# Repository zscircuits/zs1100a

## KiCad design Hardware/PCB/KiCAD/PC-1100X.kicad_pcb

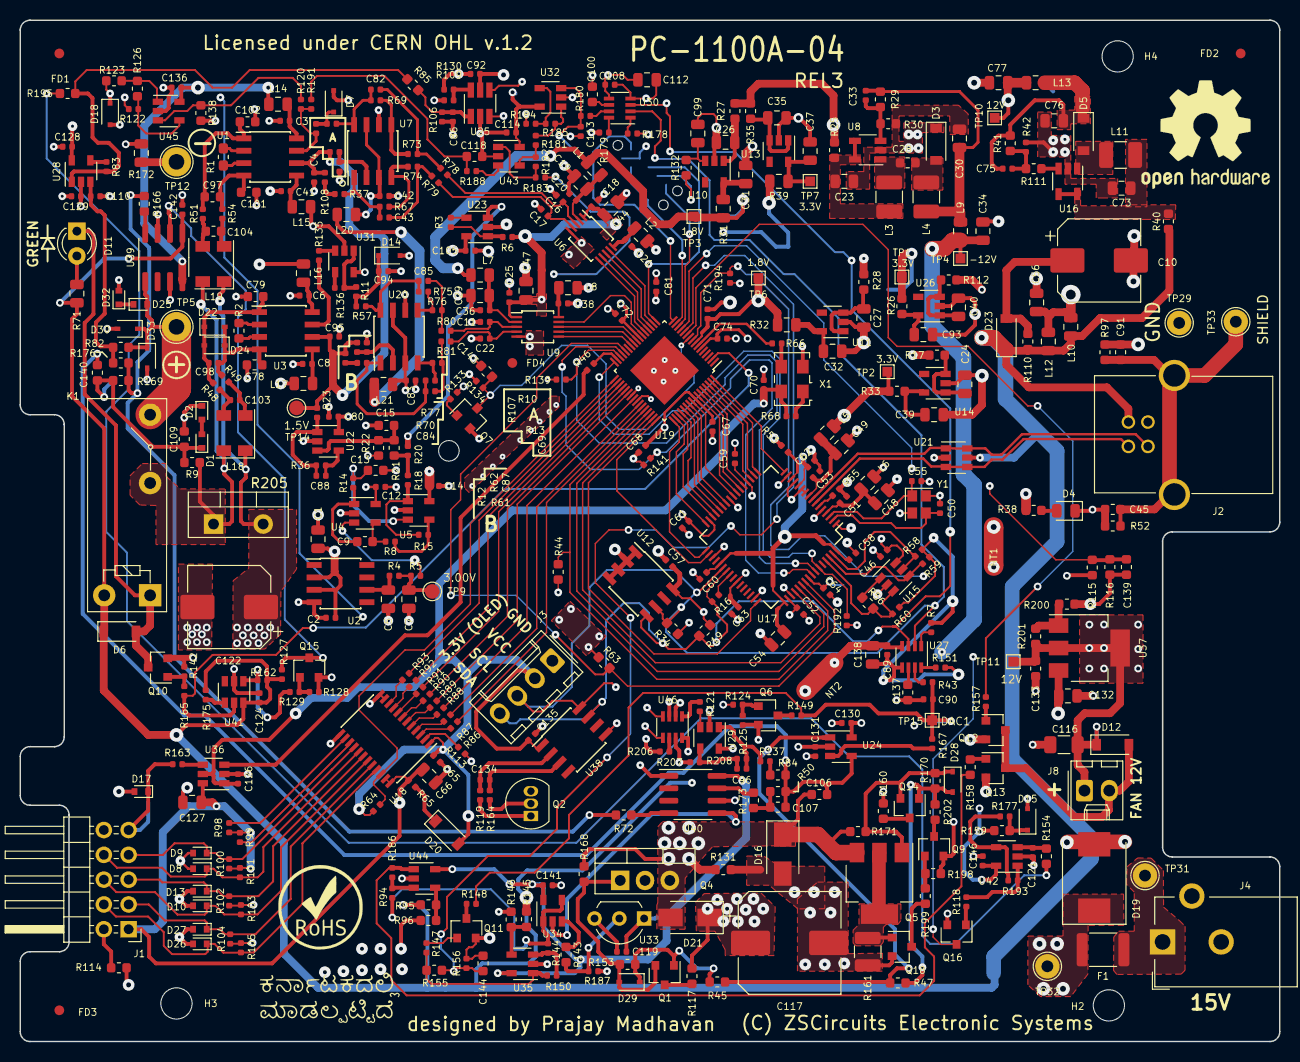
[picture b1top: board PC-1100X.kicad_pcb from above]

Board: 4 copper layers, 129.0 x 104.6 mm, 528 parts (0 on the bottom side), 290 nets.

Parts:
C1, C5, C7, C19, C24, C26, C27, C29, C30, C31, C32, C35, C37, C39, C40, C44, C47, C48, C49, C54, C66, C76, C93, C99, C112, C127, C132, C138: 10uF; C_0805_2012Metric
C2, C3, C6, C8, C12, C14, C21, C36, C38, C41, C42, C46, C52, C57, C58, C59, C60, C61, C62, C63, C64, C65, C67, C68, C70, C71, C72, C74, C80, C81, C83, C86, C89, C90, C92, C105, C108, C113, C114, C119, C121, C124, C126, C130, C131, C135, C136, C141, C142, C146: 0.1uF; C_0402_1005Metric
C4, C18, C25, C84, C85, C95, C96, C98, C103: 1000pF; C_0402_1005Metric
C9, C13, C15, C28, C45, C91, C100, C109, C118, C133, C137: 1uF; C_0603_1608Metric
C10, C122: 220uF; CP_Elec_8x10
C11, C16, C17, C22: 2200pF; C_0402_1005Metric
C20, C51, C53, C88, C94, C134: 100pF; C_0402_1005Metric
C23, C34, C56, C73, C77: 22uF; C_0805_2012Metric
C33, C43, C75, C82: 220pF; C_0402_1005Metric
C50, C55: 12pF; C_0402_1005Metric
C69, C87, C110, C128, C129: 10000pF; C_0402_1005Metric
C78, C79, C97, C101, C102, C104, C107: 100pF; C_0603_1608Metric
C106, C139, C140, C143, C144: 4700pF; C_0603_1608Metric
C116: 47uF; C_1206_3216Metric
C117: 470uF; CP_Elec_10x10
D1, D2, D8, D9, D10, D13, D17, D25, D26, D27, D32: ESD5Z12T1G; D_SOD-523
D3, D5: MBR0520; D_SOD-123
D4: LED; LED_0805_2012Metric
D6, D12, D20, D23: CDBW140-G; D_SOD-123
D7: MM3Z5V6T1G; D_SOD-323F
D11: LED GREEN; LED_D3.0mm
D14: MM3Z4V3T1G; D_SOD-323F
D15: MM3Z7V5ST1G; D_SOD-323F
D16, D21: SK56A-LTP; D_SMA
D18: MM3Z4V7ST1G; D_SOD-323F
D19: SMDJ20A; D_SMC
D22, D24, D28, D29: D_Schottky; D_SOD-323
D30, D33: 1N4148WSF-7; D_SOD-323
F1: Polyfuse; R_1812_4532Metric
FD1, FD2, FD3, FD4: FIDUCIAL; Fiducial_1mm_Dia_2.54mm_Outer_CopperTop_Paste
H2, H3, H4: MountingHole; MountingHole_3.2mm_M3
H5: MountingHole; MountingHole_2.1mm
HS1, HS2: Heatsink; NONE
J1: Conn_02x05_Odd_Even; PinHeader_2x05_P2.54mm_Horizontal
J2: USB_B; USB2p0_TypeB_Standard
J3: Conn_01x04_Male; Molex_KK-254_AE-6410-04A_1x04_P2.54mm_Vertical
J4: Barrel_Jack_Switch; BarrelJack_CUI_PJ-102AH_Horizontal_3D
J5: Conn_02x05_Counter_Clockwise; Tag-Connect_TC2050-IDC-NL_2x05_P1.27mm_Vertical
J8: Fan; Molex_KK-254_AE-6410-02A_1x02_P2.54mm_Vertical
K1: G5NB; Relay_SPST_Omron-G5NB
L1, L2, L5, L6, L7, L8, L9, L10, L12, L13, L14, L15, L16, L17, L20, L21: FB; L_0805_2012Metric
L3, L4, L11: 10uH; L_1210_3225Metric_Pad1.42x2.65mm_HandSolder
L18, L19: choke; CommonModeChoke-4Pin_4.5x3.2mm
LG2: RoHS; Rohs_09mm
LG4: Made in KA; MadeInKA_15mmx6mm
LOGO1: Logo_Open_Hardware_Small; OSHW-Logo2_14.6x12mm_SilkScreen
NT1, NT2: Net-Tie_2; NetTie-2_SMD_Pad2.0mm
P1, P3, P4, P5, P6, P7, P8, P9, P10, P11, P12, P13, P14, P15, P16, P17, P18, P19: DUMMY; NONE
P2: Aluminium Case; NONE
Q1, Q6, Q7, Q11, Q12, Q13, Q16, Q18: BC817; SOT-23
Q2: 2N3906; TO-92_Inline
Q4: TIP33C; TO-220-3_Vertical
Q5: FZT1151ATA; SOT-223-3_TabPin2
Q9, Q14: BC807; SOT-23
Q10, Q15: BSS138; SOT-23
R1: 20k00; R_0603_1608Metric_Pad1.05x0.95mm_HandSolder
R2: 56R2; R_0603_1608Metric
R3, R14, R36, R48, R49, R51, R53, R54, R83, R94, R109, R113, R119, R121, R130, R135, R136, R144, R164, R181, R188: 1k; R_0402_1005Metric
R4, R73, R74, R76, R77, R78, R79, R80, R81: 22R; R_0402_1005Metric
R5, R13, R15, R20, R62, R137, R148, R149: 0R; R_0402_1005Metric
R6, R18, R23: 2R; R_0402_1005Metric
R7, R43, R151, R157, R167, R178, R179, R180, R194: 3.3k; R_0402_1005Metric
R8, R185: 20k; R_0402_1005Metric
R9, R17, R25, R26, R27, R28, R33, R35, R40, R112, R166, R173: 0R; R_0603_1608Metric
R10, R37, R107, R108: 499R; R_0402_1005Metric
R11, R12: 1k60; R_0402_1005Metric
R16, R46, R65, R66, R86, R87, R88, R89, R90, R91, R92, R93, R163: 33R; R_0402_1005Metric
R19, R34, R45, R47: 2k2; R_0603_1608Metric
R21, R22, R198, R199: 3k3; R_0603_1608Metric
R29: 82k; R_0603_1608Metric
R30, R44, R52, R63, R72, R95, R97, R111, R126, R132, R138, R145, R155: 10k; R_0603_1608Metric
R31, R32, R39, R172: 0R; R_0805_2012Metric
R38: 330R; R_0603_1608Metric
R41: 105k; R_0603_1608Metric
R42, R55: 12k; R_0402_1005Metric
R50: 15k00; R_0603_1608Metric
R56, R116, R146, R200, R202: 2k; R_0603_1608Metric
R57, R61: 1k20; R_0402_1005Metric
R58, R59, R60, R64, R68, R120, R122, R139, R141, R162, R177, R184, R191, R192, R206, R207: 10k; R_0402_1005Metric
R67, R69: 1k00; R_0402_1005Metric
R70, R75: 6k80; R_0402_1005Metric
R71: 680R; R_0805_2012Metric
R82, R96, R123, R131, R143, R154, R159, R169, R176, R195: 1k; R_0603_1608Metric
R84, R85: 10k00; R_0603_1608Metric
R98, R99, R100, R101, R102, R103, R104, R105, R128, R142, R182, R193: 100k; R_0402_1005Metric
R106: 2k10; R_0402_1005Metric
R110, R114, R117, R160: 10R; R_0603_1608Metric
R115, R158: 6k8; R_0603_1608Metric
R118, R124, R125, R133, R147, R208: 33k; R_0402_1005Metric
R127, R129, R156, R165: 4k3; R_0402_1005Metric
R134: 3k3; R_0402_1005Metric
R150, R175, R186, R187: 47k; R_0402_1005Metric
R153, R170: 5k6; R_0603_1608Metric
R161: 1R; R_1210_3225Metric
R168, R171: 150R; R_0603_1608Metric
R183: 100R; R_0402_1005Metric
R201: 220R; R_0603_1608Metric
R205: 1R00; TO-220-2_Vertical
TP1, TP2, TP3, TP4, TP6, TP7, TP10: TestPoint; TestPoint_Pad_1.0x1.0mm
TP5, TP12: TestPoint; TestPoint_Loop_D2.60mm_Drill1.6mm_Beaded
TP8, TP9, TP13, TP14, TP16, TP17, TP18, TP19, TP20, TP21, TP22, TP23, TP24, TP25, TP26, TP27, TP28: TestPoint; TestPoint_Pad_D1.5mm
TP11, TP15: TP; TestPoint_Pad_1.0x1.0mm
TP29, TP31, TP32, TP33: TestPoint; TestPoint_THTPad_D2.5mm_Drill1.2mm
U1, U3, U40: AD8422ARZ; SOIC-8_3.9x4.9mm_P1.27mm
U2: LT1461CCS8-3; SOIC-8_3.9x4.9mm_P1.27mm
U4: OPA333xxDBV; SOT-23-5
U5, U22, U23: THS4281DBVT; SOT-23-5
U6, U9: MCP33131D-10-I/MS; TSSOP-10_3x3mm_P0.5mm
U7, U20: THS4521; SOIC-8_3.9x4.9mm_P1.27mm
U8: LT1931; TSOT-23-5
U10, U11: TLV70218_SOT23-5; SOT-23-5
U12: ATSHA204A-SSHDA-T; SOIC-8_3.9x4.9mm_P1.27mm
U13, U14, U26: TLV70233_SOT23-5; SOT-23-5
U15: 93LC46B; SOT-23-6
U16: LT1613; TSOT-23-5
U17: FT2232H; LQFP-64_10x10mm_P0.5mm
U18: SN74LVC8T245; TSSOP-24_4.4x7.8mm_P0.65mm
U19: 5M160ZE64I5N; EQFP-64_1EP_7x7mm_P0.4mm_SM
U21: USBLC6-2SC6Y; SOT-23-6
U24, U28, U29, U31, U45: OPA196; SOT-23-5
U25: MCP3425A0T-ECH; SOT-23-6_Handsoldering
U27, U30: LTC2631ITS8-LM12; SOT-23-8
U32, U34, U35, U42, U43, U44: TLV9301IDBVR; SOT-23-5
U33: LM35DZ/NOPB; TO-92L_Inline_Wide
U36: SN74LVC1T45DBVR; SOT-23-6
U37: LM317_3PinPackage; SOT-223-3_TabPin2
U38: TMP411; SOIC-8_3.9x4.9mm_P1.27mm
U39: ADG417BR; SOIC-8_3.9x4.9mm_P1.27mm
U41: TPS3808; SOT-23-6
U46: CAT5171; SOT-23-8
X1: 64MHz; Oscillator_SMD_TXC_7C-4Pin_5.0x3.2mm
Y1: Crystal 12MHz; Crystal_SMD_2520-4Pin_2.5x2.0mm

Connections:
+1V8: C71.1, C81.1, R32.1, TP6.1, TP20.1, U19.8, U19.41
+3V3: C92.1, C108.1, C112.1, L20.1, L21.1, R26.2, R179.1, TP1.1, TP25.1, U25.5, U30.5
+5V: C1.2, C2.2, C12.1, C14.1, C56.1, C80.1, C105.1, L10.2, L12.2, R38.1, U2.2, U2.3, U4.5, U5.5, U22.5, U23.5
+12P: C116.1, C133.1, D12.1, J8.1, R201.1, TP11.1, TP28.1, U37.2
+12V: C77.1, C114.1, C119.1, C128.1, C130.1, C136.1, C141.1, C146.1, L13.2, L14.1, L16.1, R159.1, TP10.1, TP24.1, U24.5, U28.5, U29.5, U31.5, U32.5, U33.1, U34.5, U35.5, U39.4, U40.8, U42.5, U43.5, U44.5, U45.5
+15V: C117.1, C132.1, D19.1, D21.1, F1.1, Q4.2, Q9.2, R115.1, R117.1, R198.2, TP32.1, U37.3
-12V: C34.1, C129.2, C131.1, L9.2, L15.2, L17.2, TP4.1, TP22.1, U24.2, U28.2, U29.2, U31.2, U34.2, U40.5
/ADC_System/ADC1_CONVST: U6.6, U19.21
/ADC_System/ADC1_DIN: U6.9, U19.18
/ADC_System/ADC1_DOUT: U6.7, U19.20
/ADC_System/ADC1_SCLK: U6.8, U19.19
/ADC_System/ADC2_CONVST: U9.6, U19.26
/ADC_System/ADC2_DIN: U9.9, U19.22
/ADC_System/ADC2_DOUT: U9.7, U19.25
/ADC_System/ADC2_SCLK: U9.8, U19.24
/ADC_System/ADC_REF_3V: C18.1, C25.1, C44.1, C47.1, R6.2, TP13.1, U6.1, U9.1
/ADC_System/CURR_LIM_SETV: R181.1, R185.2, U32.1
/ADC_System/DIV_OUT: R121.2, U46.1
/ADC_System/I2C_SCL_3V3: J3.3, R34.2, U12.6, U17.38, U25.3, U27.2, U30.2, U38.8, U46.4
/ADC_System/I2C_SDA_3V3: J3.4, R16.2, R19.2, U12.5, U17.39, U25.4, U27.3, U30.3, U38.7, U46.5
/ADC_System/ILIM_P: C118.1, R188.1, R191.2
/ADC_System/LTC_REF_CAP: C5.2, R4.1, U2.6
/ADC_System/SAR1_BUF_REF: C4.1, C95.1, R12.1, R13.1, R23.1, R62.1, R108.1, R122.1, TP14.1, TP18.1, U1.6, U3.6
/ADC_System/SAR1_INM: C17.1, R79.2, U6.4
/ADC_System/SAR1_INP: C16.1, R78.2, U6.3
/ADC_System/SENSE_M: K1.2, L18.4, L19.4, R9.2, R205.1
/ADC_System/SENSE_P: C106.1, C122.1, D16.1, D21.2, L18.1, L19.1, Q4.3, Q5.3, R131.1, R168.1, R171.2, R205.2
/CPLD_USB/ACBUS0: U17.26, U19.55
/CPLD_USB/ACBUS1: U17.27, U19.54
/CPLD_USB/ACBUS2: U17.28, U19.53
/CPLD_USB/ACBUS3: U17.29, U19.52
/CPLD_USB/ACBUS4: U17.30, U19.51
/CPLD_USB/ACBUS5: U17.32, U19.50
/CPLD_USB/ACBUS6: U17.33, U19.49
/CPLD_USB/ACBUS7: U17.34, U19.48
/CPLD_USB/ADBUS0: U17.16, U19.64
/CPLD_USB/ADBUS1: U17.17, U19.63
/CPLD_USB/ADBUS2: U17.18, U19.62
/CPLD_USB/ADBUS3: U17.19, U19.61
/CPLD_USB/ADBUS4: U17.21, U19.60
/CPLD_USB/ADBUS5: U17.22, U19.59
/CPLD_USB/ADBUS6: U17.23, U19.58
/CPLD_USB/ADBUS7: U17.24, U19.56
/CPLD_USB/BCBUS0: U17.48, U19.47
/CPLD_USB/BCBUS1: U17.52, U19.46
/CPLD_USB/BCBUS2: U17.53, U19.45
/CPLD_USB/BCBUS3: R44.2, U17.54, U19.44
/CPLD_USB/BCBUS4: R63.2, U17.55, U19.28
/CPLD_USB/BCBUS5: R141.2, U17.57, U19.29
/CPLD_USB/BCBUS6: R139.2, U17.58, U19.30
/CPLD_USB/BCBUS7: R192.2, U17.59, U19.32
/CPLD_USB/CLK_OUT: D17.1, J1.9, R163.1, TP16.1
/CPLD_USB/DIG0: R86.2, U19.43
/CPLD_USB/DIG0_IN: D26.1, J1.4, R105.2, U18.21
/CPLD_USB/DIG1: R87.2, U19.42
/CPLD_USB/DIG1_IN: D27.1, J1.3, R104.2, U18.20
/CPLD_USB/DIG2: R88.2, U19.40
/CPLD_USB/DIG2_IN: D10.1, J1.6, R103.2, U18.19
/CPLD_USB/DIG3: R89.2, U19.38
/CPLD_USB/DIG3_IN: D13.1, J1.5, R102.2, U18.18
/CPLD_USB/DIG4: R90.2, U19.37
/CPLD_USB/DIG4_IN: D8.1, J1.8, R101.2, U18.17
/CPLD_USB/DIG5: R91.2, U19.36
/CPLD_USB/DIG5_IN: D9.1, J1.7, R100.2, U18.16
/CPLD_USB/DIG6: R92.2, U19.35
/CPLD_USB/DIG7: R93.2, U19.34
/CPLD_USB/EE_CLK: R59.1, U15.4, U17.62
/CPLD_USB/EE_CS: R58.1, U15.5, U17.63
/CPLD_USB/EE_DATA: R56.1, R60.1, U15.3, U17.61
/CPLD_USB/IO_02: R165.1, U19.2, U41.5
/CPLD_USB/IO_09: Q16.3, R194.2, U19.9
/CPLD_USB/IO_10: C143.2, Q7.3, R134.2, U19.10
/CPLD_USB/IO_12: C144.2, R155.2, R156.1, U19.12
/CPLD_USB/IO_13: C139.2, R115.2, R116.1, U19.13
/CPLD_USB/LOGIC_VCC: C66.1, C127.1, J1.1, R65.2, R98.1, R99.1, R100.1, R101.1, U18.23, U18.24, U36.6
/CPLD_USB/TCK: J5.1, U19.16
/CPLD_USB/TDI: J5.9, U19.15
/CPLD_USB/TDO: J5.3, U19.17
/CPLD_USB/TMS: J5.5, U19.14
/CPLD_USB/USB_D+: J2.3, U17.8, U21.1, U21.6
/CPLD_USB/USB_D-: J2.2, U17.7, U21.3, U21.4
/CPLD_USB/VPHY: C48.1, C51.1, L6.2, U17.4
/CPLD_USB/VPLL: C49.1, C53.1, L5.2, U17.9
/CPLD_USB/~DIG_OE: R64.2, U18.22, U19.33
/OutputDriver/CLAMP_IN: R124.1, R133.1, R183.1
/OutputDriver/C_FB: C106.2, C107.2, C140.2, R50.1, R84.1, U24.4
/OutputDriver/FAN_CTRL: R94.1, R144.1, TP17.1, U34.1, U34.4
/OutputDriver/FAN_EN_3V3: R157.1, U19.11
/OutputDriver/GND_SENSE: C86.2, R106.2, R109.1, R172.2, U40.1
/OutputDriver/MUX_CONTROL: Q15.3, R127.2, U39.6
/OutputDriver/OUTPUT: D25.2, D30.1, D33.1, K1.3, R82.1, TP5.1, U39.1
/OutputDriver/VBUFF_SENSE: R154.2, R195.2
/OutputDriver/V_FB: R72.2, R166.1, R169.2, R176.1
GND: C1.1, C2.1, C3.2, C4.2, C5.1, C6.2, C7.1, C8.2, C10.2, C11.2, C12.2, C13.2, C14.2, C15.2, C16.2, C17.2, C18.2, C19.2, C20.2, C21.2, C22.2, C23.2, C24.2, C25.2, C26.2, C27.2, C29.2, C30.2, C31.2, C32.2, C34.2, C35.2, C36.2, C37.2, C38.2, C39.2, C40.2, C41.2, C42.2, C44.2, C45.2, C46.2, C47.2, C48.2, C49.2, C50.2, C51.2, C52.2, C53.2, C54.2, C55.2, C56.2, C57.2, C58.2, C59.2, C60.2, C61.2, C62.2, C63.2, C64.2, C65.2, C66.2, C67.2, C68.2, C69.2, C70.2, C71.2, C72.2, C73.2, C74.2, C76.2, C77.2, C78.1, C79.1, C80.2, C81.2, C83.2, C87.2, C89.2, C90.2, C91.2, C92.2, C93.2, C94.2, C95.2, C99.2, C100.2, C101.1, C102.1, C105.2, C108.2, C110.2, C112.2, C113.2, C114.2, C118.2, C124.2, C126.2, C127.2, C128.2, C129.1, C135.2, C136.2, C137.2, C138.2, C143.1, D3.1, D4.1, D7.2, D8.2, D9.2, D10.2, D13.2, D14.2, D17.2, D18.2, D26.2, D27.2, J1.10, J2.4, J3.1, J5.2, J5.10, NT1.1, NT2.1, Q2.3, Q7.2, Q15.2, R22.2, R30.2, R42.2, R44.1, R52.2, R55.1, R63.1, R97.2, R102.1, R103.1, R104.1, R105.1, R113.1, R114.2, R128.2, R130.2, R138.2, R139.1, R141.1, R178.2, R184.1, R192.1, TP29.1, U2.4, U4.2, U5.2, U6.5, U7.6, U8.2, U9.5, U10.2, U11.2, U12.1, U12.2, U12.3, U12.4, U13.2, U14.2, U15.2, U16.2, U17.1, U17.5, U17.10, U17.11, U17.13, U17.15, U17.25, U17.35, U17.47, U17.51, U18.11, U18.12, U18.13, U19.65, U20.6, U21.2, U22.2, U23.2, U25.2, U26.2, U27.4, U30.4, U32.2, U36.2, U38.5, U41.2, U43.2, U45.2, U46.3, X1.2, Y1.2, Y1.4
GNDREF: C109.2, C116.2, C117.2, C119.2, C121.2, C122.2, C130.2, C131.2, C132.2, C133.2, C139.1, C141.2, C142.2, C144.1, C146.2, D2.1, D15.2, D16.2, D19.2, D30.2, D32.2, D33.2, J4.2, J4.3, NT1.2, NT2.2, Q6.2, Q10.2, Q11.2, Q12.2, Q13.2, Q16.2, Q18.2, R96.2, R116.2, R125.2, R131.2, R142.2, R146.2, R156.2, R160.1, R161.1, R172.1, R187.2, R200.2, R207.2, TP12.1, U33.3, U35.2, U39.3, U39.7, U40.6, U42.2, U44.2, U46.7
unnamed: C3.1, L14.2, U1.8
unnamed: C6.1, L16.2, U3.8
unnamed: C7.2, R4.2, R5.1, TP9.1
unnamed: C8.1, L17.1, U3.5
unnamed: C9.1, R14.1, U4.1
unnamed: C9.2, R8.1, U4.4
unnamed: C10.1, D23.2, R110.2
unnamed: C11.1, R80.2, U9.3
unnamed: C13.1, R14.2, U5.3
unnamed: C15.1, R21.2, R22.1, U22.3
unnamed: C19.1, C20.1, L1.2, U6.2
unnamed: C21.1, L2.2, U6.10
unnamed: C22.1, R81.2, U9.4
unnamed: C23.1, L3.1, R25.2, U8.4, U8.5
unnamed: C24.1, R17.1, U14.1, U14.3
unnamed: C26.1, R27.1, U10.1
unnamed: C27.1, R28.1, U11.1, U11.3
unnamed: C28.1, L3.2, U8.1
unnamed: C28.2, D3.2, L4.1
unnamed: C29.1, C36.1, L7.2, U9.2
unnamed: C30.1, C33.1, L4.2, L9.1, R29.1
unnamed: C31.1, R31.2, U10.5
unnamed: C32.1, R32.2, U11.5
unnamed: C33.2, R29.2, R30.1, U8.3
unnamed: C35.1, R35.1, U13.1, U13.3
unnamed: C37.1, R39.2, TP7.1, U13.5
unnamed: C38.1, L8.2, U9.10
unnamed: C39.1, R33.1, U14.5
unnamed: C40.1, R112.1, U26.1, U26.3
unnamed: C41.1, L15.1, U1.5
unnamed: C42.1, L20.2, U7.3, U7.7
unnamed: C43.1, R74.2, R79.1
unnamed: C43.2, R37.2, R67.1, U7.1
unnamed: C45.1, C91.1, J2.5, R52.1, R97.1, TP33.1
unnamed: C50.1, U17.2, Y1.3
unnamed: C55.1, U17.3, Y1.1
unnamed: C69.1, R13.2, U7.2
unnamed: C73.1, L11.1, R40.2, U16.4, U16.5
unnamed: C75.1, C76.1, D5.1, L13.1, R41.1
unnamed: C75.2, R41.2, R42.1, R111.1
unnamed: C78.2, C98.1, D22.2, D24.1, R49.2, U3.4
unnamed: C79.2, C98.2, D22.1, D24.2, R48.2, U3.1
unnamed: C82.1, R73.2, R78.1
unnamed: C82.2, R10.2, R69.1, U7.8
unnamed: C83.1, L21.2, U20.3, U20.7
unnamed: C84.1, R77.2, R81.1
unnamed: C84.2, R61.2, R70.1, U20.1
unnamed: C85.1, R76.2, R80.1
unnamed: C85.2, R57.2, R75.1, U20.8
unnamed: C86.1, R85.2, R106.1, U25.1
unnamed: C87.1, R62.2, U20.2
unnamed: C88.1, R23.2, R36.2, U22.1
unnamed: C88.2, R36.1, U22.4
unnamed: C90.1, R43.2, R148.1, R149.1, R167.2, TP15.1, TP27.1
unnamed: C93.1, R26.1, U26.5
unnamed: C94.1, D14.1, R11.2, R57.1
unnamed: C96.1, R137.2, R208.1, U29.1
unnamed: C96.2, R207.1, R208.2, U29.4
unnamed: C99.1, R132.1, U10.3
unnamed: C100.1, U30.6
unnamed: C97.1, C101.2, R54.2, U1.4
unnamed: C97.2, C102.2, R51.2, U1.1
unnamed: C103.1, L18.2, R49.1
unnamed: C103.2, L18.3, R48.1
unnamed: C104.1, L19.2, R54.1
unnamed: C104.2, L19.3, R51.1
unnamed: C107.1, R50.2, R173.1
unnamed: C109.1, C140.1, D1.1, R9.1, R169.1, TP26.1
unnamed: C110.1, R82.2, R176.2, U28.3
unnamed: C113.1, R180.2, TP8.1, U32.3
unnamed: C121.1, R154.1, U42.3
unnamed: C134.1, R164.2, U38.3
unnamed: C134.2, R119.2, U38.2
unnamed: C137.1, U27.6
unnamed: D1.2, D2.2
unnamed: D4.2, R38.2
unnamed: D5.2, L11.2, U16.1
unnamed: D7.1, R10.1, R107.2
unnamed: D6.2, D11.1, K1.1, Q10.3
unnamed: D11.2, R71.2
unnamed: D12.2, J8.2, Q12.3, Q13.3
unnamed: D15.1, R159.2, R177.1
unnamed: D18.1, R123.1, U46.8
unnamed: D20.1, R65.1
unnamed: D25.1, D32.1
unnamed: D28.1, Q5.1, Q14.2, R170.2, R171.1
unnamed: D28.2, Q14.1, R47.1, R170.1, R202.1
unnamed: D29.1, Q1.1, R45.1, R153.2
unnamed: D29.2, Q1.2, Q4.1, R153.1, R168.2
unnamed: F1.2, J4.1, TP31.1
unnamed: J1.2, R114.1
unnamed: Q1.3, R117.2
unnamed: Q2.1, R119.1
unnamed: Q2.2, R164.1
unnamed: Q6.1, R124.2, R125.1
unnamed: Q6.3, R149.2
unnamed: Q7.1, R133.2
unnamed: Q9.1, R198.1, R199.2
unnamed: Q9.3, R202.2
unnamed: Q10.1, R142.1, R165.2
unnamed: Q11.1, R147.1
unnamed: Q11.3, R148.2
unnamed: Q12.1, R157.2
unnamed: Q13.1, R158.1
unnamed: Q14.3, R160.2
unnamed: Q15.1, R128.1, R129.2
unnamed: Q16.1, R118.1
unnamed: Q5.2, Q18.1, R161.2
unnamed: Q18.3, R199.1
unnamed: R1.1, U1.2
unnamed: R1.2, U1.3
unnamed: R2.1, U3.2
unnamed: R2.2, U3.3
unnamed: R3.1, U23.4
unnamed: R3.2, R6.1, U23.1
unnamed: R5.2, U4.3
unnamed: R7.2, U27.1
unnamed: R11.1, R136.2, U31.1
unnamed: R12.2, R61.1
unnamed: R8.2, R15.1, U5.4
unnamed: R15.2, R18.1, U5.1
unnamed: R16.1, U17.40
unnamed: R18.2, R20.1, R21.1
unnamed: R20.2, U23.3
unnamed: R43.1, U27.7
unnamed: R45.2, R47.2, U24.1
unnamed: R46.1, U36.3
unnamed: R46.2, U19.31
unnamed: R53.1, U17.14
unnamed: R55.2, U17.6
unnamed: R56.2, U15.1
unnamed: R66.1, X1.3
unnamed: R66.2, U19.7
unnamed: R67.2, R74.1, U7.4
unnamed: R68.1, X1.1
unnamed: R69.2, R73.1, U7.5
unnamed: R70.2, R77.1, U20.4
unnamed: R72.1, U40.4
unnamed: R75.2, R76.1, U20.5
unnamed: R83.1, U28.4
unnamed: R86.1, U18.3
unnamed: R87.1, U18.4
unnamed: R88.1, U18.5
unnamed: R89.1, U18.6
unnamed: R90.1, U18.7
unnamed: R91.1, U18.8
unnamed: R92.1, U18.9
unnamed: R93.1, U18.10
unnamed: R95.2, R96.1, U44.4
unnamed: R98.2, U18.14
unnamed: R99.2, U18.15
unnamed: R107.1, R120.1, R191.1, U1.7
unnamed: R37.1, R108.2
unnamed: R109.2, R130.1, U25.6
unnamed: R111.2, U16.3
unnamed: R113.2, U18.2
unnamed: R118.2, R193.2, U42.1
unnamed: R120.2, R138.1, U45.3
unnamed: R121.1, U29.3
unnamed: R122.2, R126.1, U45.4
unnamed: R123.2, R126.2, U45.1
unnamed: R129.1, R162.2, U41.1
unnamed: R135.1, U31.3
unnamed: R135.2, U3.7
unnamed: R136.1, U31.4
unnamed: R84.2, R137.1
unnamed: R143.1, U34.3
unnamed: R143.2, R187.1, U33.2
unnamed: R144.2, R150.1, U35.3
unnamed: R145.2, R146.1, U35.4
unnamed: R147.2, R150.2, R155.1, U35.1
unnamed: R151.2, U27.8
unnamed: R158.2, R186.2, U44.1
unnamed: R163.2, U36.4
unnamed: R166.2, U39.8
unnamed: R167.1, U24.3
unnamed: R173.2, U40.7
unnamed: R175.2, U41.4
unnamed: R177.2, R193.1, U42.4
unnamed: R178.1, U30.1
unnamed: R179.2, U30.8
unnamed: R180.1, U30.7
unnamed: R181.2, R182.1, U43.4
unnamed: R182.2, R183.2, U43.1
unnamed: R184.2, R185.1, U32.4
unnamed: R94.2, R186.1, U44.3
unnamed: R188.2, U43.3
unnamed: R83.2, R85.1, R195.1, U28.1
unnamed: R200.1, R201.2, U37.1
unnamed: R206.2, U46.6
USB3V3: C46.1, C52.1, C57.1, C59.1, C61.1, C63.1, C64.1, C67.1, C68.1, C89.1, C138.1, L5.1, L6.1, R7.1, R19.1, R33.2, R34.1, R53.2, R58.2, R59.2, R60.2, R151.1, TP2.1, TP23.1, U12.8, U15.6, U17.20, U17.31, U17.42, U17.50, U17.56, U19.39, U19.57, U27.5
VAA: L1.1, L7.1, R31.1, TP3.1, TP19.1
VBUS5V: C124.1, C142.1, D6.1, D23.1, J2.1, K1.5, L10.1, L12.1, R17.2, R25.1, R27.2, R28.2, R35.2, R40.1, R71.1, R95.1, R110.1, R112.2, R127.1, R145.1, R162.1, R175.1, U21.5, U39.5, U41.6, U46.2
VCCIO: C65.1, C70.1, C72.1, C74.1, C126.1, C135.1, D20.2, J3.2, J5.4, L2.1, L8.1, R39.1, R64.1, R68.2, R132.2, R134.1, R194.1, R206.1, TP21.1, U18.1, U19.6, U19.23, U36.1, U36.5, U38.1, X1.4
VDD: C54.1, C58.1, C60.1, C62.1, U17.12, U17.37, U17.49, U17.64

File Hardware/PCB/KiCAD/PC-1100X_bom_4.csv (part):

Component,References,Value,Footprint,Quantity Per PCB,Description,Part,MPN,Manufacturer,ALT_PN,Assembly,Tolerance,Frequency
1,C2 C3 C6 C8 C12 C14 C21 C36 C38 C41 C42 C46 C52 C57 C58 C59 C60 C61 C62 C63 C64 C65 C67 C68 C70 C71 C72 C74 C80 C81 C83 C86 C89 C90 C92 C105 C108 C113 C114 C119 C121 C124 C126 C130 C131 C135 C136 C141 C142 C146,0.1uF,C_0402_1005Metric,50,Unpolarized capacitor,C,TMK105B7104MV-FR,Samsung,,,,
2,C69 C87 C110 C128 C129,10000pF,C_0402_1005Metric,5,Unpolarized capacitor,C,TMF105B7103MVHF,,,,,
3,C4 C18 C25 C84 C85 C95 C96 C98 C103,1000pF,C_0402_1005Metric,9,Unpolarized capacitor,C,C0402C102J5RAC7411,Kemet,,,,
4,C78 C79 C97 C101 C102 C104 C107,100pF,C_0603_1608Metric,7,Unpolarized capacitor,C,C0603C101K5RACTU,Kemet,,,,
5,C20 C51 C53 C88 C94 C134,100pF,C_0402_1005Metric,6,Unpolarized capacitor,C,C0402C101J3GACTU,Kemet,,,,
6,C1 C5 C7 C19 C24 C26 C27 C29 C30 C31 C32 C35 C37 C39 C40 C44 C47 C48 C49 C54 C66 C76 C93 C99 C112 C127 C132 C138,10uF,C_0805_2012Metric,28,Unpolarized capacitor,C,TMK212BBJ106MGHT,,,,,
7,C50 C55,12pF,C_0402_1005Metric,2,Unpolarized capacitor,C,GJM1555C1H120FB01D,,,,,
8,C9 C13 C15 C28 C45 C91 C100 C109 C118 C133 C137,1uF,C_0603_1608Metric,11,Unpolarized capacitor,C,TMK107BJ105KA-T,,CL10A105KA8NNNC,,,
9,C11 C16 C17 C22,2200pF,C_0402_1005Metric,4,Unpolarized capacitor,C,C0402C222J3GACTU,,,,,
10,C33 C43 C75 C82,220pF,C_0402_1005Metric,4,Unpolarized capacitor,C,CC0402JRNPO8BN221,,,,,
11,C10 C122,220uF,CP_Elec_8x10,2,Polarized capacitor,CP,UWT1E221MNL1GS,,,,,
12,C23 C34 C56 C73 C77,22uF,C_0805_2012Metric,5,Unpolarized capacitor,C,GRM21BR61E226ME44L,,,,,
13,C106 C139 C140 C143 C144,4700pF,C_0603_1608Metric,5,Unpolarized capacitor,C,C0603C472K5RACTU,Kemet,,,,
14,C117,470uF,CP_Elec_10x10,1,Polarized capacitor,CP,UWT1E471MNL1GS,,,,,
15,C116,47uF,C_1206_3216Metric,1,Unpolarized capacitor,C,EMK316BBJ476ML-T,,,,,
16,D30 D33,1N4148WSF-7,D_SOD-323,2,"75V 0.15A Fast switching Diode, SOD-323",1N4148WS,1N4148WSF-7,,,,,
17,D6 D12 D20 D23,CDBW140-G,D_SOD-123,4,Schottky diode,D_Schottky,CDBW140-G,,,,,
18,D22 D24 D28 D29,D_Schottky,D_SOD-323,4,Schottky diode,D_Schottky,BAT54HT1G,,,,,
19,D1 D2 D8 D9 D10 D13 D17 D25 D26 D27 D32,ESD5Z12T1G,D_SOD-523,11,Zener diode,D_Zener,ESD5Z12T1G,,,,,
20,D4,LED,LED_0805_2012Metric,1,Light emitting diode,LED,LTST-C170KRKT,,,,,
21,D11,LED GREEN,LED_D3.0mm,1,Light emitting diode,LED,151031VS06000,,,,,
22,D3 D5,MBR0520,D_SOD-123,2,"20V 0.5A Schottky Power Rectifier Diode, SOD-123",MBR0520,MBR0520LT3G,MC Semiconductor,,,,
23,D14,MM3Z4V3T1G,D_SOD-323F,1,Zener diode,D_Zener,MM3Z4V3T1G,,,,,
24,D18,MM3Z4V7ST1G,D_SOD-323F,1,Zener diode,D_Zener,MM3Z4V7ST1G,,,,,
25,D7,MM3Z5V6T1G,D_SOD-323F,1,Zener diode,D_Zener,MM3Z5V6T1G,,,,,
26,D15,MM3Z7V5ST1G,D_SOD-323F,1,Zener diode,D_Zener,MM3Z7V5ST1G,,,,,
27,D16 D21,SK56A-LTP,D_SMA,2,Schottky diode,D_Schottky,SK56A-LTP,,SBR3U20SA-13,,,
28,D19,SMDJ20A,D_SMC,1,Zener diode,D_Zener,SMDJ20A,,,,,
29,F1,Polyfuse,R_1812_4532Metric,1,"Resettable fuse, polymeric positive temperature coefficient",Polyfuse,0ZCG0150FF2C,,,,,
30,HS1,Heatsink,NONE,1,Heatsink,Heatsink,577002B00000G,577002B00000G,,,,
31,HS2,Heatsink,NONE,1,Heatsink,Heatsink,507302B00000G,507302B00000G,,,,
32,J4,Barrel_Jack_Switch,BarrelJack_CUI_PJ-102AH_Horizontal_3D,1,DC Barrel Jack with an internal switch,Barrel_Jack_Switch,PJ-102AH,,,,,
33,J3,Conn_01x04_Male,Molex_KK-254_AE-6410-04A_1x04_P2.54mm_Vertical,1,"Generic connector, single row, 01x04, script generated (kicad-library-utils/schlib/autogen/connector/)",Conn_01x04_Male,22-27-2041,Molex,,,,
34,J5,Conn_02x05_Counter_Clockwise,Tag-Connect_TC2050-IDC-NL_2x05_P1.27mm_Vertical,1,"Generic connector, double row, 02x05, counter clockwise pin numbering scheme (similar to DIP packge numbering), script generated (kicad-library-utils/schlib/autogen/connector/)",Conn_02x05_Counter_Clockwise,,,,<DNP>,,
35,J1,Conn_02x05_Odd_Even,PinHeader_2x05_P2.54mm_Horizontal,1,"Generic connector, double row, 02x05, odd/even pin numbering scheme (row 1 odd numbers, row 2 even numbers), script generated (kicad-library-utils/schlib/autogen/connector/)",Conn_02x05_Odd_Even,10129382-910001BLF,,,,,
36,J8,Fan,Molex_KK-254_AE-6410-02A_1x02_P2.54mm_Vertical,1,Fan,Fan,22-27-2021,Molex,,,,
37,J2,USB_B,USB2p0_TypeB_Standard,1,USB Type B connector,USB_B,SS-52300-001,On Shore,SS-52300-001,,,
38,K1,G5NB,Relay_SPST_Omron-G5NB,1,"Omron G5Q relay, Miniature Single Pole, SPST-NO, 10A",G5Q-1A,G5NB-1A4-DC5,,,,,
39,L3 L4 L11,10uH,L_1210_3225Metric_Pad1.42x2.65mm_HandSolder,3,Inductor,L,LQH32PN100MN0L,,,,,
40,L1 L2 L5 L6 L7 L8 L9 L10 L12 L13 L14 L15 L16 L17 L20 L21,FB,L_0805_2012Metric,16,Ferrite bead,Ferrite_Bead,MPZ2012S601AT000,TDK,,,,
41,L18 L19,choke,CommonModeChoke-4Pin_4.5x3.2mm,2,Coupled inductor,L_Coupled,744235601,,,,,
42,LG4,Made in KA,MadeInKA_15mmx6mm,1,,LOGO,,,,<DNP>,,
43,LG2,RoHS,Rohs_09mm,1,,LOGO,,,,<DNP>,,
44,LOGO1,Logo_Open_Hardware_Small,OSHW-Logo2_14.6x12mm_SilkScreen,1,"Open Hardware logo, small",Logo_Open_Hardware_Small,,,,,,
45,NT1 NT2,Net-Tie_2,NetTie-2_SMD_Pad2.0mm,2,"Net tie, 2 pins",Net-Tie_2,,,,,,
46,P2,Aluminium Case,NONE,1,,DUMMY-IOT_PS_Library-ZS-2102A-02-rescue,AK-C-C28,SZOMK,,<ACC>,,
47,P1,DUMMY,NONE,1,,DUMMY-IOT_PS_Library-ZS-2102A-02-rescue,418-TRH70A15011E02VI,,,<ACC>,,
48,P10,DUMMY,NONE,1,,DUMMY-IOT_PS_Library-ZS-2102A-02-rescue,ASB0312LA-CF00,Delta Electronics,,<ACC>,,
49,P11,DUMMY,NONE,1,,DUMMY-IOT_PS_Library-ZS-2102A-02-rescue,"SSD1306 I2C OLED 0.96"" MODULE WHITE",Molex,,<ACC>,,
50,P12,DUMMY,NONE,1,,DUMMY,Nut M2 (8 Qty),,,<ACC>,,
51,P13,DUMMY,NONE,1,,DUMMY,Molex cable 4 pin,,,<ACC>,,
52,P14,DUMMY,NONE,1,,DUMMY,Button head Bolt M3x16 (4 Qty),,,<ACC>,,
53,P15,DUMMY,NONE,1,,DUMMY,Nut M3 (4 Qty),,,<ACC>,,
54,P16,DUMMY,NONE,1,,DUMMY,Molex cable 2-pin,,,<ACC>,,
55,P17,DUMMY,NONE,1,,DUMMY,Bumpon 12x5mm (Qty = 4),Hukimoyo,,<ACC>,,
56,P18,DUMMY,NONE,1,,DUMMY,Nut M3 (2 Qty),,,<ACC>,,
57,P19,DUMMY,NONE,1,,DUMMY,441-R311-GRX,,,<ACC>,,
58,P3,DUMMY,NONE,1,,DUMMY-IOT_PS_Library-ZS-2102A-02-rescue,CBLT-UA-UB-1,CUI,,<ACC>,,
59,P4,DUMMY,NONE,1,,DUMMY-IOT_PS_Library-ZS-2102A-02-rescue,Banana Cable Black,Any,,<ACC>,,
60,P5,DUMMY,NONE,1,,DUMMY-IOT_PS_Library-ZS-2102A-02-rescue,Banana cable Red,Any,,<ACC>,,
61,P6,DUMMY,NONE,1,,DUMMY,Button head Bolt M3x8 (2 Qty),,,<ACC>,,
62,P7,DUMMY,NONE,1,,DUMMY-IOT_PS_Library-ZS-2102A-02-rescue,111-0102-001,Cinch Connectivity,,<ACC>,,
63,P8,DUMMY,NONE,1,,DUMMY-IOT_PS_Library-ZS-2102A-02-rescue,111-0103-001,Cinch Connectivity,,<ACC>,,
64,P9,DUMMY,NONE,1,,DUMMY,Button head bolt M2x6 (4 Qty),,,<ACC>,,
65,Q2,2N3906,TO-92_Inline,1,"-0.2A Ic, -40V Vce, Small Signal PNP Transistor, TO-92",2N3906,2N3906-AP,,,,,
66,Q9 Q14,BC807,SOT-23,2,"0.8A Ic, 45V Vce, PNP Transistor, SOT-23",BC807,BC807-40LT1G,,,,,
67,Q1 Q6 Q7 Q11 Q12 Q13 Q16 Q18,BC817,SOT-23,8,"0.8A Ic, 45V Vce, NPN Transistor, SOT-23",BC817,"BC817-25,235",,,,,
68,Q10 Q15,BSS138,SOT-23,2,"50V Vds, 0.22A Id, N-Channel MOSFET, SOT-23",BSS138,BSS138K-13,,,,,
69,Q5,FZT1151ATA,SOT-223-3_TabPin2,1,"-6A Ic, -100V Vce, Power PNP Transistor, TO-220",TIP42C,FZT1151ATA,,,,,
70,Q4,TIP33C,TO-220-3_Vertical,1,"6A Ic, 100V Vce, Power NPN Transistor, TO-220",TIP41C,TIP33C,,,,,
71,R9 R17 R25 R26 R27 R28 R33 R35 R40 R112 R166 R173,0R,R_0603_1608Metric,12,"Resistor, US symbol",R_US,RC0603JR-070RL,,,,1%,
72,R5 R13 R15 R20 R62 R137 R148 R149,0R,R_0402_1005Metric,8,"Resistor, US symbol",R_US,RC0402JR-070RL,,,,1%,
73,R31 R32 R39 R172,0R,R_0805_2012Metric,4,"Resistor, US symbol",R_US,RC0805JR-070RL,,,,1%,
74,R183,100R,R_0402_1005Metric,1,"Resistor, US symbol",R_US,RC0402FR-07100RL,,,,1%,
75,R98 R99 R100 R101 R102 R103 R104 R105 R128 R142 R182 R193,100k,R_0402_1005Metric,12,"Resistor, US symbol",R_US,RC0402FR-07100KL,,,,1%,
76,R41,105k,R_0603_1608Metric,1,"Resistor, US symbol",R_US,RC0603FR-07105KL,,,,1%,
77,R110 R114 R117 R160,10R,R_0603_1608Metric,4,"Resistor, US symbol",R_US,RC0603FR-0710RL,,,,1%,
78,R30 R44 R63 R72 R95 R111 R126 R132 R138 R145 R155,10k,R_0603_1608Metric,11,"Resistor, US symbol",R_US,RC0603FR-0710KL,,,,1%,
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
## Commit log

2020-12-03 Added documents
    Added SDoc documents
2020-12-03 Added certification charts
    Added certification charts
2020-12-06 Most files uploaded
    Hardware design files, User Guide, sDoc etc
2020-12-06 Updated CERN OHL
    Added License File
2020-12-06 V7
    Removed the ZSCircuits logo from the enclosure
2021-02-11 Ver 2.7.1
    1. Fixed a bug in the reading of the HW revision, when the slowPC was enabled.
2021-02-15 Ver 2.7.1.1
    1. Peiodically flushed the I2C data to prevent overflow. Useful across very long runs spanning several hours.
2021-02-16 Ver 2.7.11
    Minor fix to flush I2C data periodically.
2021-07-04 Delete ZS-1100-A-CE-SDOC.pdf
    Old document
2021-07-04 New CE SDoC
    Updated to latest direcrtives
2022-03-29 Ver 2.7.5 (Viewer only mode supported)
    Now supports viewing the data files without the hardware connected.
    C:\Program Files (x86)\ZSCircuits\IOTPowerProfiler\IOTPowerViewer.exe

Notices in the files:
Hardware/PCB/KiCAD/PC-1100X.kicad_pcb:
Copyright ZSCircuits Electronic Systems Pvt Ltd ( 2020 )
This documentation describes Open Hardware and is licensed under the
CERN OHL v. 1.2.
Licensed under CERN OHL v.1.2
